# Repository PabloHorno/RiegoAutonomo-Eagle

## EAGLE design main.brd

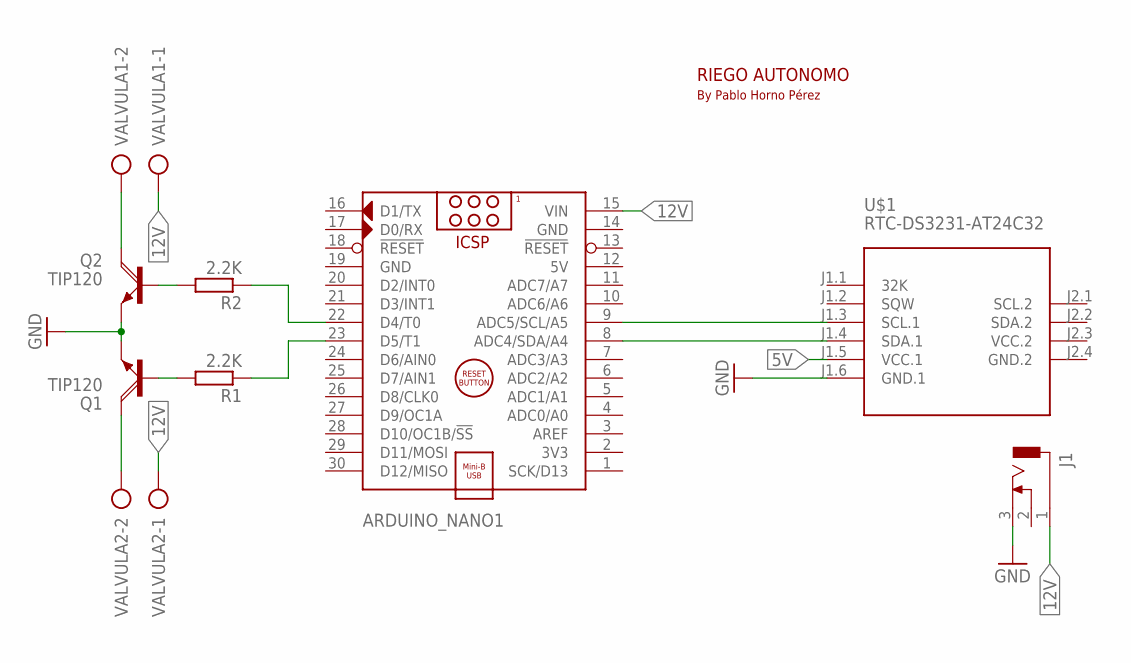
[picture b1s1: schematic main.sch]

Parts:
ARDUINO_NANO1: ARDUINO_NANO
J1: DCJ0303
Q1, Q2: TIP120; TO220AH
R1, R2: 2.2K; 0207/10
U$1: RTC-DS3231-AT24C32
VALVULA1, VALVULA2: AK500/2

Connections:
5V: ARDUINO_NANO1.12 (5V), U$1.J1.5 (VCC.1)
12V: ARDUINO_NANO1.15 (VIN), J1.1, VALVULA1.1, VALVULA2.1
GND: ARDUINO_NANO1.14 (GND), ARDUINO_NANO1.19 (GND), J1.3, Q1.E, Q2.E, U$1.J1.6 (GND.1)
GND.2: U$1.J2.4 (GND.2)
unnamed: Q2.B, R2.2
unnamed: Q1.B, R1.2
unnamed: ARDUINO_NANO1.8 (ADC4/SDA/A4), U$1.J1.4 (SDA.1)
unnamed: ARDUINO_NANO1.9 (ADC5/SCL/A5), U$1.J1.3 (SCL.1)
unnamed: Q1.C, VALVULA2.2
unnamed: Q2.C, VALVULA1.2
unnamed: ARDUINO_NANO1.23 (D5/T1), R1.1
unnamed: ARDUINO_NANO1.22 (D4/T0), R2.1
VCC.2: U$1.J2.3 (VCC.2)

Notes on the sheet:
RIEGO AUTONOMO
By Pablo Horno Pérez

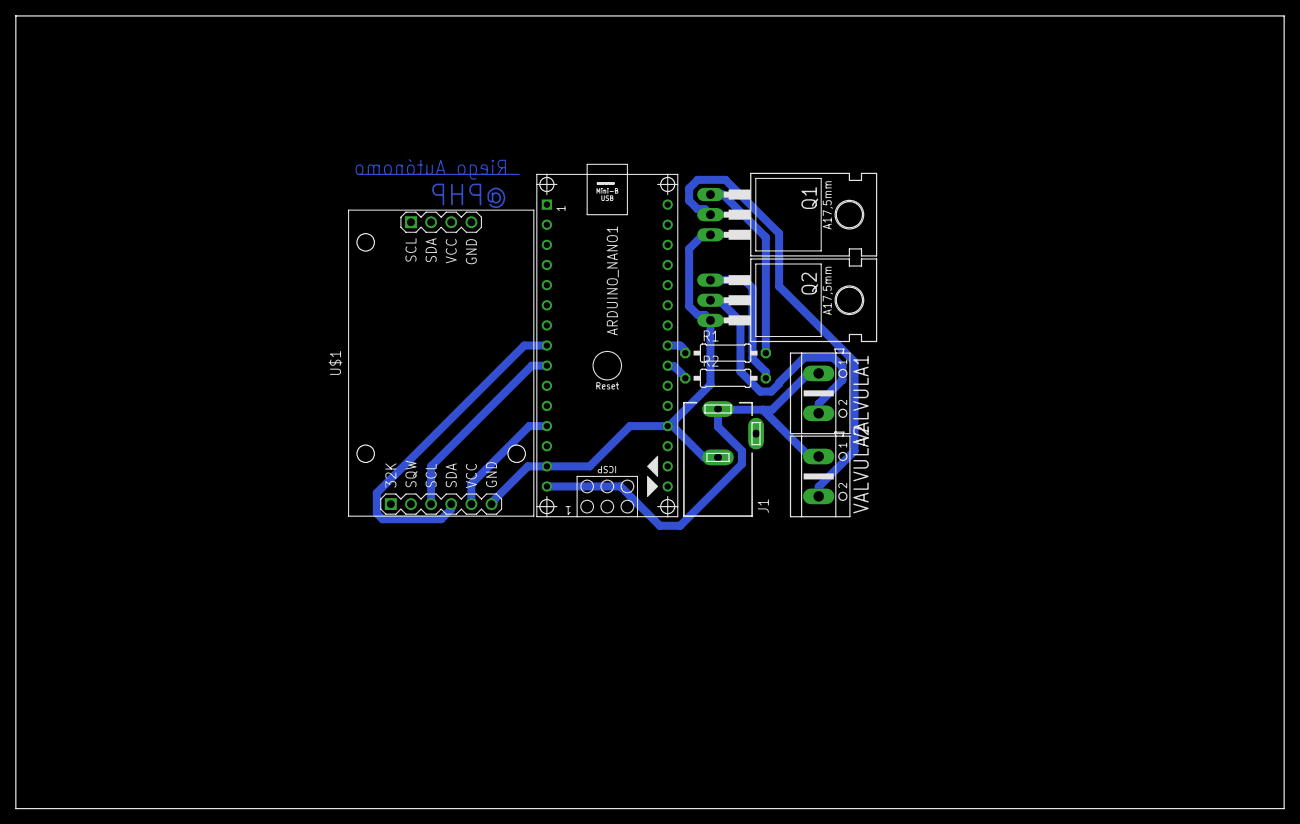
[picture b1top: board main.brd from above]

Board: 2 copper layers, 160.0 x 100.0 mm, 9 parts (0 on the bottom side), 11 nets.

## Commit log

2017-08-25 Añadido led 5mm
2017-08-25 test
2017-08-27 Final PCB
    Agregado componente RTC, rutado y listo para fabricacion
2017-08-28 Modificacion de PCB
    Reduccion de espacio moviendo los transistores TIP120

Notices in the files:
parts and their libraries:
diy-modules: Released under the Creative Commons Attribution 4.0 International License: http://creativecommons.org/licenses/by/4.0
